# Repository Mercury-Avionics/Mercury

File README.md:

# Mercury
Integrated Avionics Package for Rocket and UAV Needs
Built on STM32 F4

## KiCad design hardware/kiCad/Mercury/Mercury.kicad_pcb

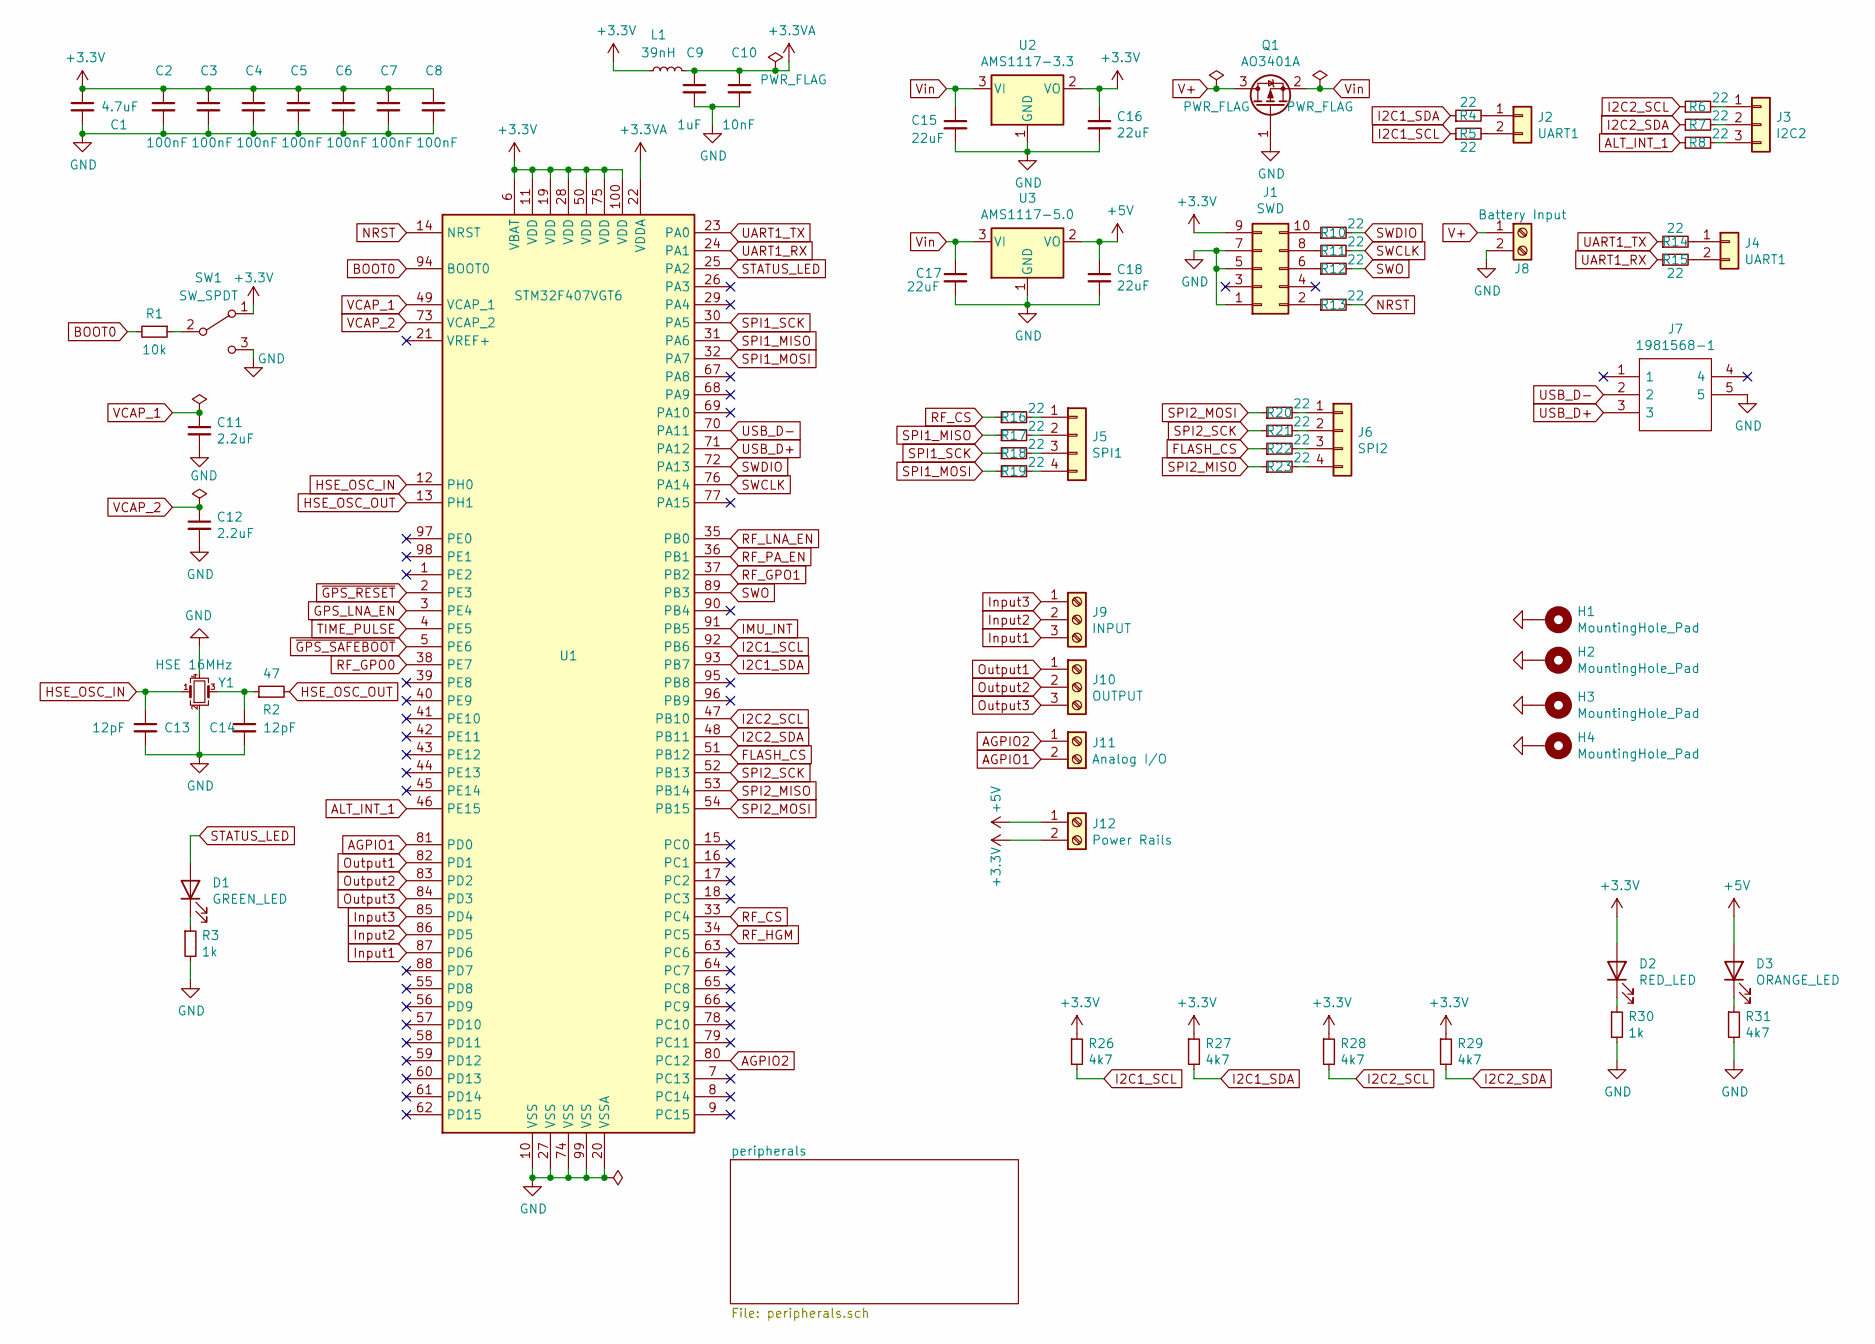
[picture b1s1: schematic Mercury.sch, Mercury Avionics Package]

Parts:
C1: 4.7uF; C_0805_2012Metric; LCSC Part # C1779
C2, C3, C4, C5, C6, C7, C8: 100nF; C_0402_1005Metric; LCSC Part # C1525
C9: 1uF; C_0402_1005Metric; LCSC Part # C52923
C10: 10nF; C_0402_1005Metric; LCSC Part # C15195
C11, C12: 2.2uF; C_0603_1608Metric; LCSC Part # C23630
C13, C14: 12pF; C_0402_1005Metric; LCSC Part # C1547
C15, C16, C17, C18: 22uF; C_0805_2012Metric; LCSC Part # C45783
D1: GREEN_LED; LED_0603_1608Metric; LCSC Part # C72043
D2: RED_LED; LED_0603_1608Metric; LCSC Part # C2286
D3: ORANGE_LED; LED_0603_1608Metric; LCSC Part # C375450
H1, H2, H3, H4: MountingHole_Pad; MountingHole_3mm_Pad_Via
J1: SWD; PinHeader_2x05_P1.27mm_Vertical
J2, J4: UART1; SolderWire-0.1sqmm_1x02_P3.6mm_D0.4mm_OD1mm
J3: I2C2; SolderWire-0.1sqmm_1x03_P3.6mm_D0.4mm_OD1mm
J5: SPI1; SolderWire-0.1sqmm_1x04_P3.6mm_D0.4mm_OD1mm
J6: SPI2; SolderWire-0.1sqmm_1x04_P3.6mm_D0.4mm_OD1mm
J7: 1981568-1; Mouser Part Number 571-1981568-1
J8: Battery Input; TerminalBlock_Phoenix_MKDS-1,5-2-5.08_1x02_P5.08mm_Horizont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
J9: INPUT; TerminalBlock_Phoenix_MKDS-1,5-3-5.08_1x03_P5.08mm_Horizont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
J10: OUTPUT; TerminalBlock_Phoenix_MKDS-1,5-3-5.08_1x03_P5.08mm_Horizont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
J11: Analog I/O; TerminalBlock_Phoenix_MKDS-1,5-2-5.08_1x02_P5.08mm_Horizont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
J12: Power Rails; TerminalBlock_Phoenix_MKDS-1,5-2-5.08_1x02_P5.08mm_Horizont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
L1: 39nH; L_0402_1005Metric; LCSC Part # C26443
Q1: AO3401A; SOT-23; LCSC Part # C15127
R1: 10k; R_0402_1005Metric; LCSC Part # C25744
R2: 47; R_0805_2012Metric; LCSC Part # C17714
R3, R30: 1k; R_0402_1005Metric; LCSC Part # C11702
R4, R5, R6, R7, R8, R10, R11, R12, R13, R14, R15, R16, R17, R18, R19, R20, R21, R22, R23: 22; R_0402_1005Metric; LCSC Part # C25092
R26, R27, R28, R29, R31: 4k7; R_0402_1005Metric; LCSC Part # C25900
SW1: SW_SPDT; SW_CuK_OS102011MA1QN1_SPDT_Angled
U1: STM32F407VGT6; LQFP-100_14x14mm_P0.5mm; LCSC Part # C12345
U2: AMS1117-3.3; SOT-223-3_TabPin2; LCSC Part # C6186
U3: AMS1117-5.0; SOT-223-3_TabPin2; LCSC Part # C6187
Y1: HSE 16MHz; Crystal_SMD_3225-4Pin_3.2x2.5mm; LCSC Part # C13738

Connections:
+3.3VA: C9.1, C10.1, L1.2, U1.22 (VDDA)
+3V3: C1.1, C2.1, C3.1, C4.1, C5.1, C6.1, C7.1, C8.1, C16.1, D2.2 (A), J1.9, J12.2, L1.1, R26.1, R27.1, R28.1, R29.1, SW1.1 (A), U1.6 (VBAT), U1.11 (VDD), U1.19 (VDD), U1.28 (VDD), U1.50 (VDD), U1.75 (VDD), U1.100 (VDD), U2.2 (VO); also elsewhere on the board
+5V: C18.1, D3.2 (A), J12.1, U3.2 (VO)
AGPIO1: J11.2, U1.81 (PD0)
AGPIO2: J11.1, U1.80 (PC12)
ALT_INT_1: R8.1, U1.46 (PE15); also elsewhere on the board
BOOT0: R1.2, U1.94 (BOOT0)
FLASH_CS: R22.1, U1.51 (PB12); also elsewhere on the board
GND: C1.2, C2.2, C3.2, C4.2, C5.2, C6.2, C7.2, C8.2, C9.2, C10.2, C11.2, C12.2, C13.2, C14.2, C15.2, C16.2, C17.2, C18.2, H1.1, H2.1, H3.1, H4.1, J1.1, J1.5, J1.7, J7.5, J8.2, Q1.1 (G), R3.2, R30.2, R31.2, SW1.3 (C), U1.10 (VSS), U1.20 (VSSA), U1.27 (VSS), U1.74 (VSS), U1.99 (VSS), U2.1 (GND), U3.1 (GND), Y1.2, Y1.4; also elsewhere on the board
GPS_LNA_EN: U1.3 (PE4); also elsewhere on the board
HSE_OSC_IN: C13.1, U1.12 (PH0), Y1.1
HSE_OSC_OUT: R2.2, U1.13 (PH1)
I2C1_SCL: R5.1, R26.2, U1.92 (PB6); also elsewhere on the board
I2C1_SDA: R4.1, R27.2, U1.93 (PB7); also elsewhere on the board
I2C2_SCL: R6.1, R28.2, U1.47 (PB10); also elsewhere on the board
I2C2_SDA: R7.1, R29.2, U1.48 (PB11); also elsewhere on the board
IMU_INT: U1.91 (PB5); also elsewhere on the board
Input1: J9.3, U1.87 (PD6)
Input2: J9.2, U1.86 (PD5)
Input3: J9.1, U1.85 (PD4)
NRST: R13.2, U1.14 (NRST)
unnamed: C14.1, R2.1, Y1.3
unnamed: D1.1 (K), R3.1
unnamed: D2.1 (K), R30.1
unnamed: D3.1 (K), R31.1
unnamed: J1.2, R13.1
unnamed: J1.6, R12.1
unnamed: J1.8, R11.1
unnamed: J1.10, R10.1
unnamed: J2.1, R4.2
unnamed: J2.2, R5.2
unnamed: J3.1, R6.2
unnamed: J3.2, R7.2
unnamed: J3.3, R8.2
unnamed: J4.1, R14.2
unnamed: J4.2, R15.2
unnamed: J5.1, R16.2
unnamed: J5.2, R17.2
unnamed: J5.3, R18.2
unnamed: J5.4, R19.2
unnamed: J6.1, R20.2
unnamed: J6.2, R21.2
unnamed: J6.3, R22.2
unnamed: J6.4, R23.2
unnamed: R1.1, SW1.2 (B)
Output1: J10.1, U1.82 (PD1)
Output2: J10.2, U1.83 (PD2)
Output3: J10.3, U1.84 (PD3)
RF_CS: R16.1, U1.33 (PC4); also elsewhere on the board
RF_GPO0: U1.38 (PE7); also elsewhere on the board
RF_GPO1: U1.37 (PB2); also elsewhere on the board
RF_HGM: U1.34 (PC5); also elsewhere on the board
RF_LNA_EN: U1.35 (PB0); also elsewhere on the board
RF_PA_EN: U1.36 (PB1); also elsewhere on the board
SPI1_MISO: R17.1, U1.31 (PA6); also elsewhere on the board
SPI1_MOSI: R19.1, U1.32 (PA7); also elsewhere on the board
SPI1_SCK: R18.1, U1.30 (PA5); also elsewhere on the board
SPI2_MISO: R23.1, U1.53 (PB14); also elsewhere on the board
SPI2_MOSI: R20.1, U1.54 (PB15); also elsewhere on the board
SPI2_SCK: R21.1, U1.52 (PB13); also elsewhere on the board
STATUS_LED: D1.2 (A), U1.25 (PA2)
SWCLK: R11.2, U1.76 (PA14)
SWDIO: R10.2, U1.72 (PA13)
SWO: R12.2, U1.89 (PB3)
TIME_PULSE: U1.4 (PE5); also elsewhere on the board
UART1_RX: R15.1, U1.24 (PA1); also elsewhere on the board
UART1_TX: R14.1, U1.23 (PA0); also elsewhere on the board
USB_D+: J7.3, U1.71 (PA12)
USB_D-: J7.2, U1.70 (PA11)
V+: J8.1, Q1.3 (D)
VCAP_1: C11.1, U1.49 (VCAP_1)
VCAP_2: C12.1, U1.73 (VCAP_2)
Vin: C15.1, C17.1, Q1.2 (S), U2.3 (VI), U3.3 (VI)
~GPS_RESET: U1.2 (PE3); also elsewhere on the board
~GPS_SAFEBOOT: U1.5 (PE6); also elsewhere on the board

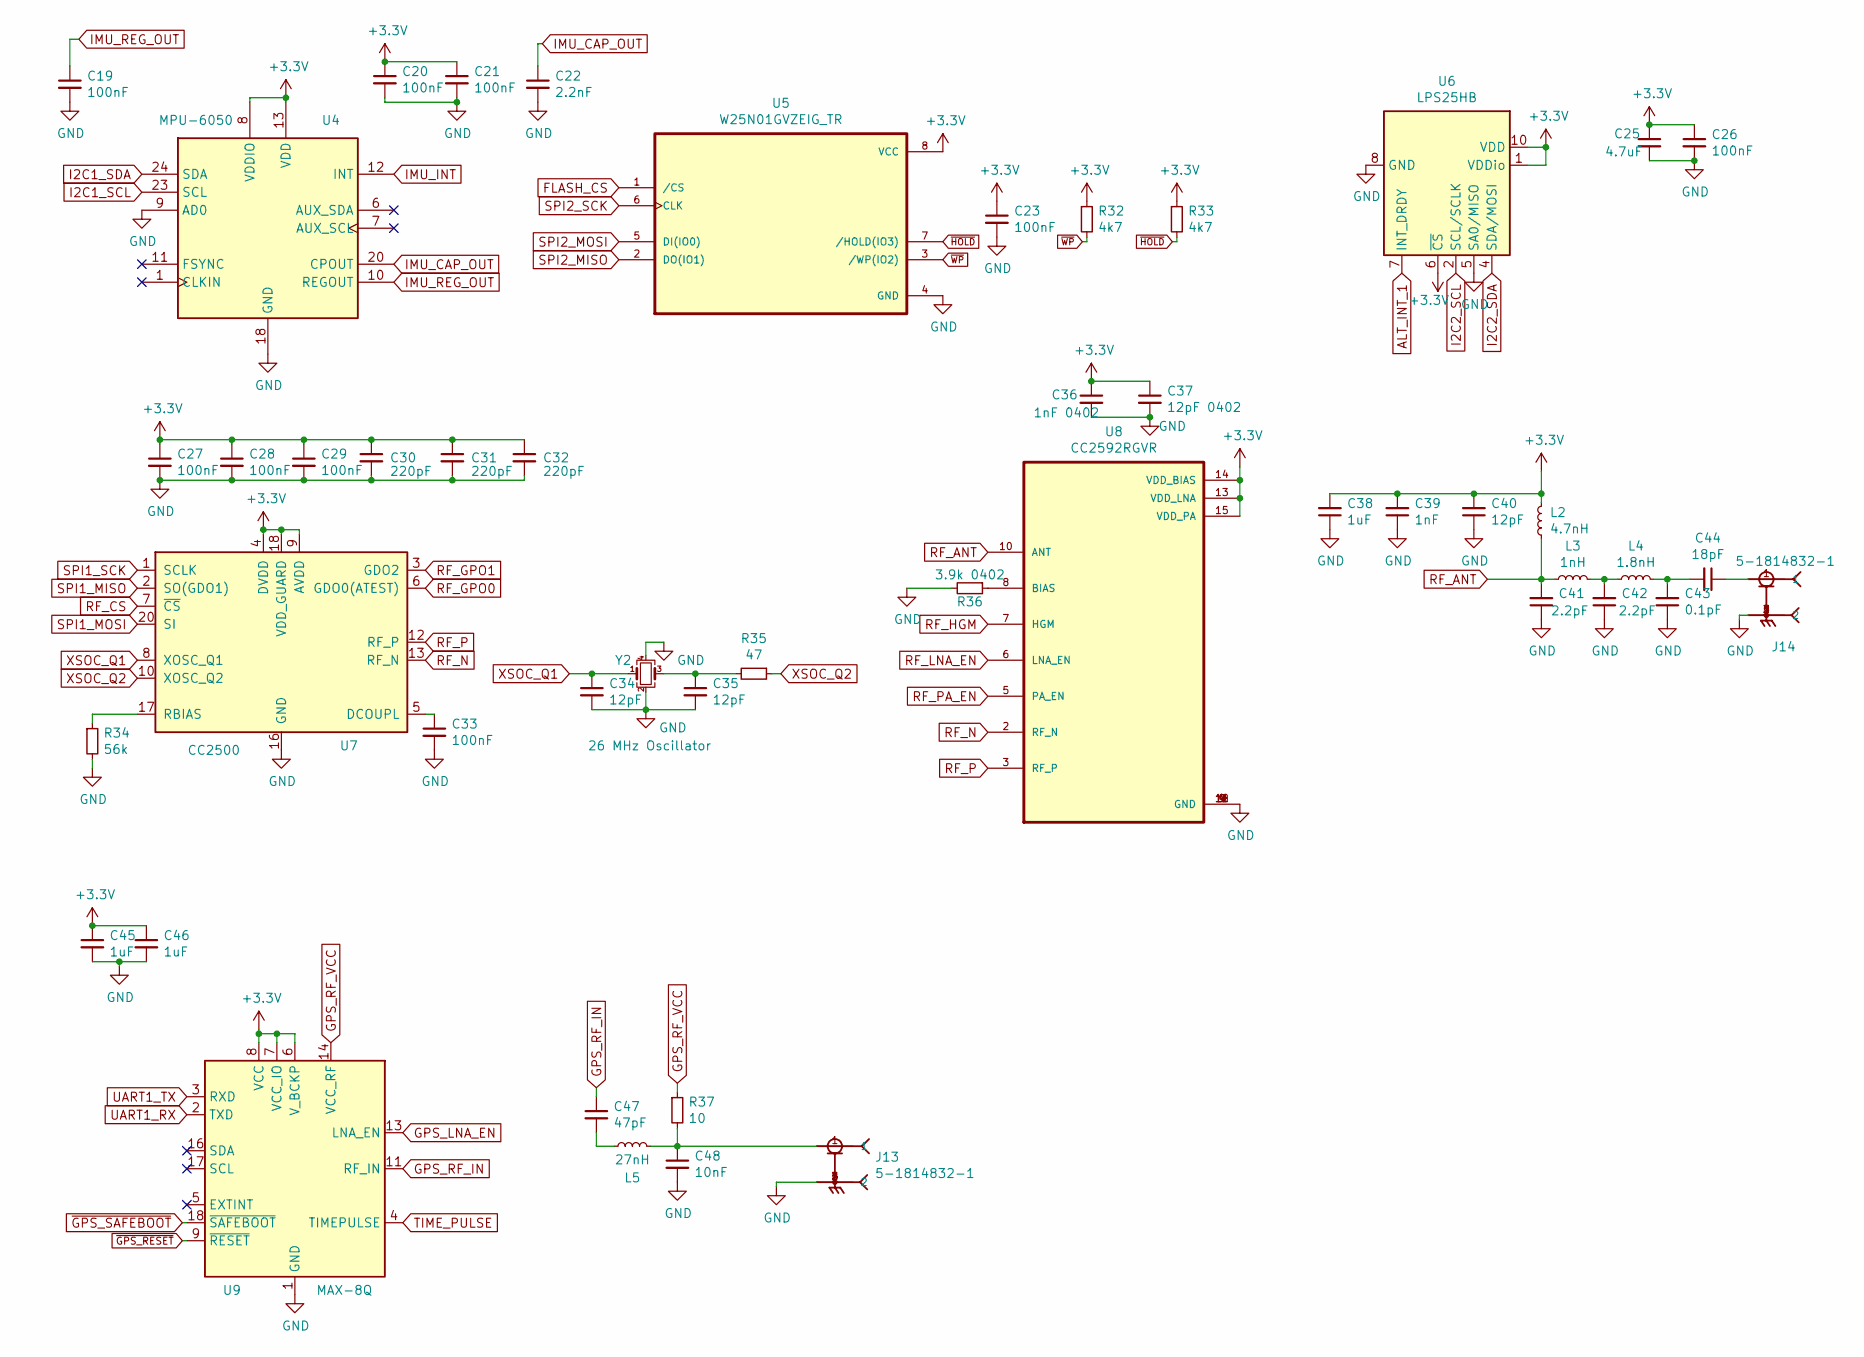
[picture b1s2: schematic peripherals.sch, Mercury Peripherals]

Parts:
C19, C20, C21, C23, C27, C28, C29, C33: 100nF; C_0402_1005Metric; LCSC Part # C1525
C22: 2.2nF; C_0603_1608Metric; LCSC Part # C1604
C25: 4.7uF; C_0805_2012Metric; LCSC Part # C1779
C26: 100nF; C_0603_1608Metric; LCSC Part # C14663
C30, C31, C32: 220pF; C_0402_1005Metric; LCSC Part # C1530
C34, C35, C40: 12pF; C_0402_1005Metric; LCSC Part # C1547
C36: 1nF 0402; C_0402_1005Metric; LCSC Part # C1523
C37: 12pF 0402; C_0402_1005Metric; LCSC Part # C1547
C38, C45, C46: 1uF; C_0402_1005Metric; LCSC Part # C52923
C39: 1nF; C_0402_1005Metric; LCSC Part # C1523
C41, C42: 2.2pF; C_0402_1005Metric; LCSC Part # C1559
C43: 0.1pF; C_0402_1005Metric; LCSC Part # C161338
C44: 18pF; C_0402_1005Metric; LCSC Part # C1549
C47: 47pF; C_0402_1005Metric; LCSC Part # C1567
C48: 10nF; C_0402_1005Metric; LCSC Part # C15195
J13, J14: 5-1814832-1; TE_5-1814832-1
L2: 4.7nH; L_0402_1005Metric; LCSC Part # C13595
L3: 1nH; L_0402_1005Metric; LCSC Part # C18222
L4: 1.8nH; L_0402_1005Metric; LCSC Part # C18304
L5: 27nH; L_0402_1005Metric; LCSC Part # C18830
R32, R33: 4k7; R_0402_1005Metric; LCSC Part # C25900
R34: 56k; R_0402_1005Metric; LCSC Part # C25796
R35: 47; R_0402_1005Metric; LCSC Part # C25118
R36: 3.9k 0402; R_0402_1005Metric; LCSC Part # C51721
R37: 10; R_0402_1005Metric; LCSC Part # C25744
U4: MPU-6050; InvenSense_QFN-24_4x4mm_P0.5mm; LCSC Part # C24112
U5: W25N01GVZEIG_TR; SON127P800X600X80-9N; LCSC Part # C88868
U6: LPS25HB; ST_HLGA-10_2.5x2.5mm_P0.6mm_LayoutBorder3x2y; LCSC Part # C87898
U7: CC2500; Texas_S-PVQFN-N20_EP2.4x2.4mm; LCSC Part # C57494
U8: CC2592RGVR; QFN65P400X400X100-17N; LCSC Part # C53274
U9: MAX-8Q; ublox_MAX
Y2: 26 MHz Oscillator; Crystal_SMD_3225-4Pin_3.2x2.5mm; LCSC Part # C23425

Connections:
+3V3: C20.1, C21.1, C23.1, C25.1, C26.1, C27.1, C28.1, C29.1, C30.1, C31.1, C32.1, C36.1, C37.1, C38.2, C39.2, C40.2, C45.1, C46.1, L2.2, R32.1, R33.1, U4.8 (VDDIO), U4.13 (VDD), U5.8 (VCC), U6.1 (VDDio), U6.6 (~CS), U6.10 (VDD), U7.4 (DVDD), U7.9 (AVDD), U7.11 (AVDD), U7.14 (AVDD), U7.15 (AVDD), U7.18 (VDD_GUARD), U8.13 (VDD_LNA), U8.14 (VDD_BIAS), U8.15 (VDD_PA), U9.6 (V_BCKP), U9.7 (VCC_IO), U9.8 (VCC); also elsewhere on the board
ALT_INT_1: U6.7 (INT_DRDY); also elsewhere on the board
FLASH_CS: U5.1 (/CS); also elsewhere on the board
GND: C19.2, C20.2, C21.2, C22.2, C23.2, C25.2, C26.2, C27.2, C28.2, C29.2, C30.2, C31.2, C32.2, C33.2, C34.2, C35.2, C36.2, C37.2, C38.1, C39.1, C40.1, C41.1, C42.1, C43.1, C45.2, C46.2, C48.2, J13.2, J13.3 (2), J13.4 (2), J13.5 (2), J14.2, J14.3 (2), J14.4 (2), J14.5 (2), R34.2, R36.2, U4.9 (AD0), U4.18 (GND), U5.4 (GND), U6.3 (GND), U6.5 (SA0/MISO), U6.8 (GND), U6.9 (GND), U7.16 (GND), U7.19 (GND), U7.21 (GND), U8.1 (GND), U8.4 (GND), U8.9 (GND), U8.11 (GND), U8.12 (GND), U8.16 (GND), U9.1 (GND), U9.10 (GND), U9.12 (GND), Y2.2, Y2.4; also elsewhere on the board
GPS_LNA_EN: U9.13 (LNA_EN); also elsewhere on the board
GPS_RF_IN: C47.1, U9.11 (RF_IN)
GPS_RF_VCC: R37.1, U9.14 (VCC_RF)
I2C1_SCL: U4.23 (SCL); also elsewhere on the board
I2C1_SDA: U4.24 (SDA); also elsewhere on the board
I2C2_SCL: U6.2 (SCL/SCLK); also elsewhere on the board
I2C2_SDA: U6.4 (SDA/MOSI); also elsewhere on the board
IMU_CAP_OUT: C22.1, U4.20 (CPOUT)
IMU_INT: U4.12 (INT); also elsewhere on the board
IMU_REG_OUT: C19.1, U4.10 (REGOUT)
unnamed: C33.1, U7.5 (DCOUPL)
unnamed: C35.1, R35.2, Y2.3
unnamed: C42.2, L3.2, L4.1
unnamed: C43.2, C44.2, L4.2
unnamed: C44.1, J14.1
unnamed: C47.2, L5.1
unnamed: C48.1, J13.1, L5.2, R37.2
unnamed: R34.1, U7.17 (RBIAS)
unnamed: R36.1, U8.8 (BIAS)
RF_ANT: C41.2, L2.1, L3.1, U8.10 (ANT)
RF_CS: U7.7 (~CS~); also elsewhere on the board
RF_GPO0: U7.6 (GDO0(ATEST)); also elsewhere on the board
RF_GPO1: U7.3 (GDO2); also elsewhere on the board
RF_HGM: U8.7 (HGM); also elsewhere on the board
RF_LNA_EN: U8.6 (LNA_EN); also elsewhere on the board
RF_N: U7.13 (RF_N), U8.2 (RF_N)
RF_P: U7.12 (RF_P), U8.3 (RF_P)
RF_PA_EN: U8.5 (PA_EN); also elsewhere on the board
SPI1_MISO: U7.2 (SO(GDO1)); also elsewhere on the board
SPI1_MOSI: U7.20 (SI); also elsewhere on the board
SPI1_SCK: U7.1 (SCLK); also elsewhere on the board
SPI2_MISO: U5.2 (DO(IO1)); also elsewhere on the board
SPI2_MOSI: U5.5 (DI(IO0)); also elsewhere on the board
SPI2_SCK: U5.6 (CLK); also elsewhere on the board
TIME_PULSE: U9.4 (TIMEPULSE); also elsewhere on the board
UART1_RX: U9.2 (TXD); also elsewhere on the board
UART1_TX: U9.3 (RXD); also elsewhere on the board
XSOC_Q1: C34.1, U7.8 (XOSC_Q1), Y2.1
XSOC_Q2: R35.1, U7.10 (XOSC_Q2)
~GPS_RESET: U9.9 (~RESET); also elsewhere on the board
~GPS_SAFEBOOT: U9.18 (~SAFEBOOT); also elsewhere on the board
~HOLD: R33.2, U5.7 (/HOLD(IO3))
~WP: R32.2, U5.3 (/WP(IO2))

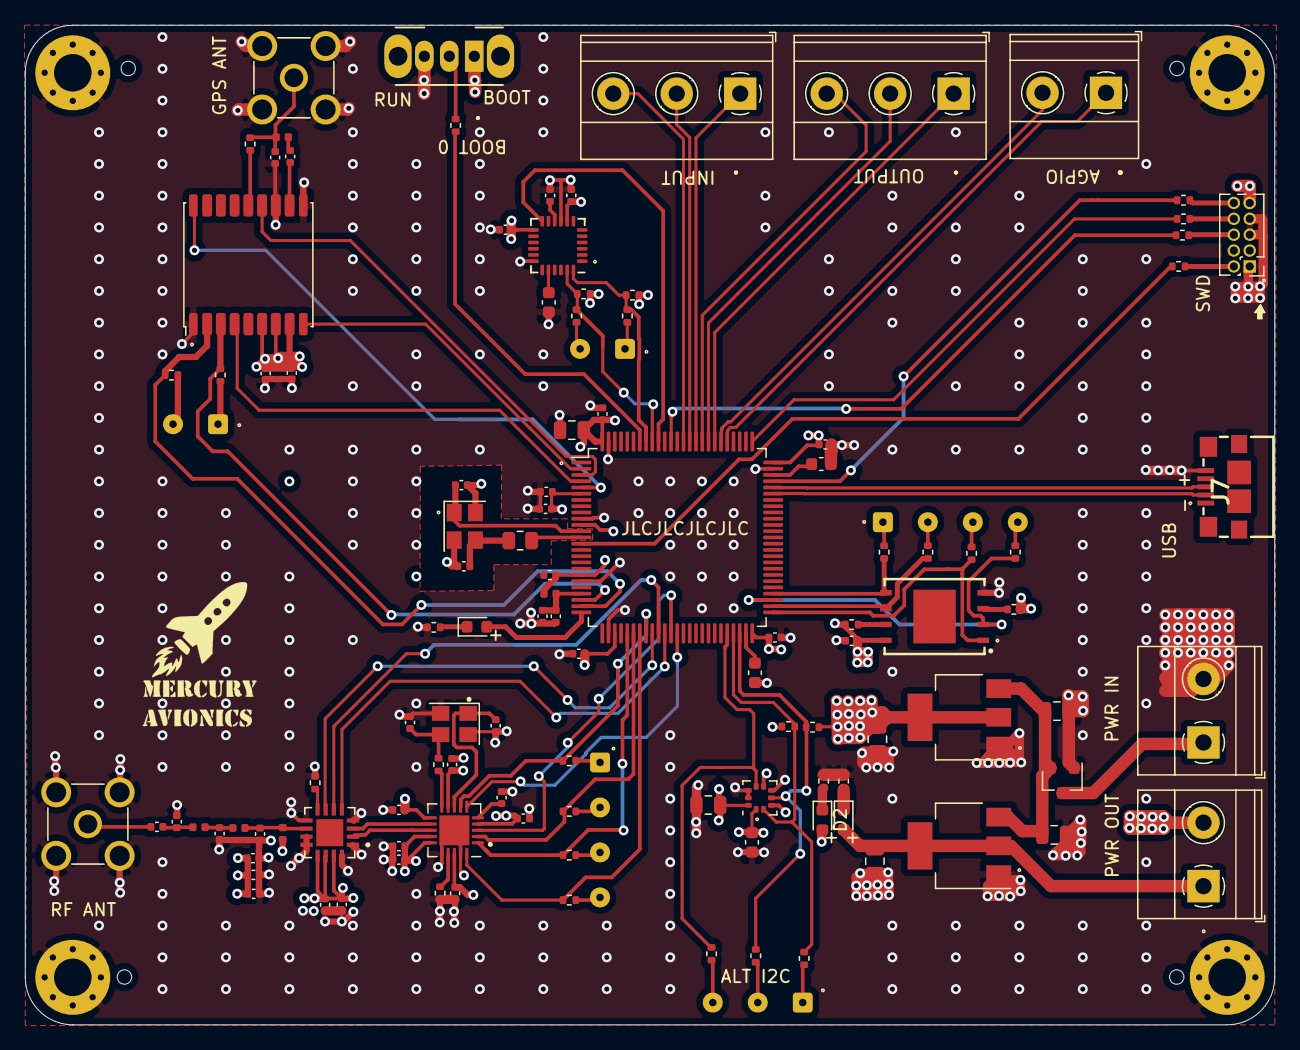
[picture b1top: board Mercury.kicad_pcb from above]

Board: 4 copper layers, 100.0 x 80.0 mm, 121 parts (0 on the bottom side), 95 nets.

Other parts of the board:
G1: LOGO

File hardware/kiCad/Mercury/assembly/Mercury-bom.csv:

Comment,Designator,Footprint,LCSC Part #
"4.7uF Unpolarized capacitor, small symbol","C1,C25",C_0805_2012Metric,C1779
"100nF Unpolarized capacitor, small symbol","C2,C3,C4,C5,C6,C7,C8,C19,C20,C21,C23,C27,C28,C29,C33",C_0402_1005Metric,C1525
"1uF Unpolarized capacitor, small symbol","C9,C38,C45,C46",C_0402_1005Metric,C52923
"10nF Unpolarized capacitor, small symbol","C10,C48",C_0402_1005Metric,C15195
"2.2uF Unpolarized capacitor, small symbol","C11,C12",C_0603_1608Metric,C23630
"12pF Unpolarized capacitor, small symbol","C13,C14,C34,C35,C40",C_0402_1005Metric,C1547
"22uF Unpolarized capacitor, small symbol","C15,C16,C17,C18",C_0805_2012Metric,C45783
"2.2nF Unpolarized capacitor, small symbol",C22,C_0603_1608Metric,C1604
"100nF Unpolarized capacitor, small symbol",C26,C_0603_1608Metric,C14663
"220pF Unpolarized capacitor, small symbol","C30,C31,C32",C_0402_1005Metric,C1530
"1nF 0402 Unpolarized capacitor, small symbol",C36,C_0402_1005Metric,C1523
"12pF 0402 Unpolarized capacitor, small symbol",C37,C_0402_1005Metric,C1547
"1nF Unpolarized capacitor, small symbol",C39,C_0402_1005Metric,C1523
"2.2pF Unpolarized capacitor, small symbol","C41,C42",C_0402_1005Metric,C1559
"0.1pF Unpolarized capacitor, small symbol",C43,C_0402_1005Metric,C161338
"18pF Unpolarized capacitor, small symbol",C44,C_0402_1005Metric,C1549
"47pF Unpolarized capacitor, small symbol",C47,C_0402_1005Metric,C1567
GREEN_LED Light emitting diode,D1,LED_0603_1608Metric,C72043
RED_LED Light emitting diode,D2,LED_0603_1608Metric,C2286
ORANGE_LED Light emitting diode,D3,LED_0603_1608Metric,C375450
MountingHole_Pad Mounting Hole with connection,"H1,H2,H3,H4",MountingHole_3mm_Pad_Via,
"SWD Generic connector, double row, 02x05, odd/even pin numbering scheme (row 1 odd numbers, row 2 even numbers), script generated (kicad-library-utils/schlib/autogen/connector/)",J1,PinHeader_2x05_P1.27mm_Vertical,
"UART1 Generic connector, single row, 01x02, script generated (kicad-library-utils/schlib/autogen/connector/)","J2,J4",SolderWire-0.1sqmm_1x02_P3.6mm_D0.4mm_OD1mm,
"I2C2 Generic connector, single row, 01x03, script generated (kicad-library-utils/schlib/autogen/connector/)",J3,SolderWire-0.1sqmm_1x03_P3.6mm_D0.4mm_OD1mm,
"SPI1 Generic connector, single row, 01x04, script generated (kicad-library-utils/schlib/autogen/connector/)",J5,SolderWire-0.1sqmm_1x04_P3.6mm_D0.4mm_OD1mm,
"SPI2 Generic connector, single row, 01x04, script generated (kicad-library-utils/schlib/autogen/connector/)",J6,SolderWire-0.1sqmm_1x04_P3.6mm_D0.4mm_OD1mm,
1981568-1 ,J7,1981568-1,
"Battery Input Generic screw terminal, single row, 01x02, script generated (kicad-library-utils/schlib/autogen/connector/)",J8,"TerminalBlock_Phoenix_MKDS-1,5-2-5.08_1x02_P5.08mm_Horizontal",
"INPUT Generic screw terminal, single row, 01x03, script generated (kicad-library-utils/schlib/autogen/connector/)",J9,"TerminalBlock_Phoenix_MKDS-1,5-3-5.08_1x03_P5.08mm_Horizontal",
"OUTPUT Generic screw terminal, single row, 01x03, script generated (kicad-library-utils/schlib/autogen/connector/)",J10,"TerminalBlock_Phoenix_MKDS-1,5-3-5.08_1x03_P5.08mm_Horizontal",
"Analog I/O Generic screw terminal, single row, 01x02, script generated (kicad-library-utils/schlib/autogen/connector/)",J11,"TerminalBlock_Phoenix_MKDS-1,5-2-5.08_1x02_P5.08mm_Horizontal",
"Power Rails Generic screw terminal, single row, 01x02, script generated (kicad-library-utils/schlib/autogen/connector/)",J12,"TerminalBlock_Phoenix_MKDS-1,5-2-5.08_1x02_P5.08mm_Horizontal",
5-1814832-1 ,"J13,J14",TE_5-1814832-1,
"39nH Inductor, small symbol",L1,L_0402_1005Metric,C26443
"4.7nH Inductor, small symbol",L2,L_0402_1005Metric,C13595
"1nH Inductor, small symbol",L3,L_0402_1005Metric,C18222
"1.8nH Inductor, small symbol",L4,L_0402_1005Metric,C18304
"27nH Inductor, small symbol",L5,L_0402_1005Metric,C18830
"AO3401A -4.0A Id, -30V Vds, P-Channel MOSFET, SOT-23",Q1,SOT-23,C15127
"10k Resistor, small symbol",R1,R_0402_1005Metric,C25744
"47 Resistor, small symbol",R2,R_0805_2012Metric,C17714
"1k Resistor, small symbol","R3,R30",R_0402_1005Metric,C11702
"22 Resistor, small symbol","R4,R5,R6,R7,R8,R10,R11,R12,R13,R14,R15,R16,R17,R18,R19,R20,R21,R22,R23",R_0402_1005Metric,C25092
"4k7 Resistor, small symbol","R26,R27,R28,R29,R31,R32,R33",R_0402_1005Metric,C25900
"56k Resistor, small symbol",R34,R_0402_1005Metric,C25796
"47 Resistor, small symbol",R35,R_0402_1005Metric,C25118
"3.9k 0402 Resistor, small symbol",R36,R_0402_1005Metric,C51721
"10 Resistor, small symbol",R37,R_0402_1005Metric,C25744
"SW_SPDT Switch, single pole double throw",SW1,SW_CuK_OS102011MA1QN1_SPDT_Angled,
"STM32F407VGT6 ARM Cortex-M4 MCU, 1024KB flash, 128KB RAM, 168MHz, 1.8-3.6V, 82 GPIO, LQFP-100",U1,LQFP-100_14x14mm_P0.5mm,C12345
"AMS1117-3.3 1A Low Dropout regulator, positive, 3.3V fixed output, SOT-223",U2,SOT-223-3_TabPin2,C6186
"AMS1117-5.0 1A Low Dropout regulator, positive, 5.0V fixed output, SOT-223",U3,SOT-223-3_TabPin2,C6187
"MPU-6050 InvenSense 6-Axis Motion Sensor, Gyroscope, Accelerometer, I2C",U4,InvenSense_QFN-24_4x4mm_P0.5mm,C24112
W25N01GVZEIG_TR ,U5,SON127P800X600X80-9N,C88868
"LPS25HB MEMS pressure sensor, 260-1260 hPa, absolute digital output baromeeter",U6,ST_HLGA-10_2.5x2.5mm_P0.6mm_LayoutBorder3x2y,C87898
"CC2500 Single Chip Low Power RF Transceiver, QFN-20",U7,Texas_S-PVQFN-N20_EP2.4x2.4mm,C57494
CC2592RGVR ,U8,QFN65P400X400X100-17N,C53274
"MAX-8Q GNSS Module M8, VCC 2.7V to 3.6V",U9,ublox_MAX,
"HSE 16MHz Four pin crystal, GND on pins 2 and 4, small symbol",Y1,Crystal_SMD_3225-4Pin_3.2x2.5mm,C13738
"26 MHz Oscillator Four pin crystal, GND on pins 2 and 4, small symbol",Y2,Crystal_SMD_3225-4Pin_3.2x2.5mm,C23425

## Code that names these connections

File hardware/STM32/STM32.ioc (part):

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Mcu.Name=STM32F407V(E-G)Tx
Mcu.Package=LQFP100
Mcu.UserName=STM32F407VGTx
PA0-WKUP.Mode=Asynchronous
PA0-WKUP.Signal=UART4_TX
PA1.Mode=Asynchronous
PA1.Signal=UART4_RX
PA11.Mode=Device_Only
PA11.Signal=USB_OTG_FS_DM
PA12.Mode=Device_Only
PA12.Signal=USB_OTG_FS_DP
PA13.Mode=Trace_Asynchronous_SW
PA13.Signal=SYS_JTMS-SWDIO
PA14.Mode=Trace_Asynchronous_SW
PA14.Signal=SYS_JTCK-SWCLK
PA2.Signal=GPIO_Output
PA5.Mode=Full_Duplex_Master
PA5.Signal=SPI1_SCK
PA6.Mode=Full_Duplex_Master
PA6.Signal=SPI1_MISO
PA7.Mode=Full_Duplex_Master
PA7.Signal=SPI1_MOSI
PA8.GPIOParameters=GPIO_Label
PA8.GPIO_Label=GPS_RESET
PA8.Signal=GPIO_Output
PB0.GPIOParameters=GPIO_Label
PB0.GPIO_Label=RF_LNA_EN
PB0.Signal=GPIO_Output
PB1.GPIOParameters=GPIO_Label
PB1.GPIO_Label=RF_PA_EN
PB1.Signal=GPIO_Output
PB10.Mode=I2C
PB10.Signal=I2C2_SCL
PB11.Mode=I2C
PB11.Signal=I2C2_SDA
PB12.GPIOParameters=GPIO_Label
PB12.GPIO_Label=FLASH_CS
PB12.Signal=GPIO_Output
PB13.Mode=Full_Duplex_Master
PB13.Signal=SPI2_SCK
PB14.Mode=Full_Duplex_Master
PB14.Signal=SPI2_MISO
PB15.Mode=Full_Duplex_Master
PB15.Signal=SPI2_MOSI
PB2.GPIOParameters=GPIO_Label
PB2.GPIO_Label=RF_GPO1
PB2.Signal=GPIO_Input
PB3.Mode=Trace_Asynchronous_SW
PB3.Signal=SYS_JTDO-SWO
PB5.GPIOParameters=GPIO_Label
PB5.GPIO_Label=IMU_INT
PB5.Signal=GPIO_Input
PB6.Mode=I2C
PB6.Signal=I2C1_SCL
PB7.Mode=I2C
PB7.Signal=I2C1_SDA
PC12.GPIOParameters=GPIO_Label
PC12.GPIO_Label=AGPIO2
PC12.Signal=GPIO_Analog
PC4.GPIOParameters=GPIO_Label
PC4.GPIO_Label=RF_CS
PC4.Signal=GPIO_Output
PC5.GPIOParameters=GPIO_Label
PC5.GPIO_Label=RF_HGM
PC5.Signal=GPIO_Output
PC7.GPIOParameters=GPIO_Label
PC7.GPIO_Label=GPS_SAFEBOOT
PC7.Signal=GPIO_Output
PC8.GPIOParameters=GPIO_Label
PC8.GPIO_Label=LNA_EN
PC8.Signal=GPIO_Output
PC9.GPIOParameters=GPIO_Label
PC9.GPIO_Label=TIME_PULSE
PC9.Signal=GPIO_Input
PD0.GPIOParameters=GPIO_Label
PD0.GPIO_Label=AGPIO1
PD0.Signal=GPIO_Analog
PD1.GPIOParameters=GPIO_Label
PD1.GPIO_Label=Output3
PD1.Signal=GPIO_Output
PD2.GPIOParameters=GPIO_Label
PD2.GPIO_Label=Output2
PD2.Signal=GPIO_Output
PD3.GPIOParameters=GPIO_Label
PD3.GPIO_Label=Output1
PD3.Signal=GPIO_Output
PD4.GPIOParameters=GPIO_Label
PD4.GPIO_Label=Input3
PD4.Signal=GPIO_Input
PD5.GPIOParameters=GPIO_Label
PD5.GPIO_Label=Input2
PD5.Signal=GPIO_Input
PD6.GPIOParameters=GPIO_Label
PD6.GPIO_Label=Input1
PD6.Signal=GPIO_Input
PE14.GPIOParameters=GPIO_Label
PE14.GPIO_Label=ALT_INT_2
PE14.Signal=GPIO_Output
PE15.GPIOParameters=GPIO_Label
PE15.GPIO_Label=ALT_INT_1
PE15.Signal=GPIO_Output
PE7.GPIOParameters=GPIO_Label
PE7.GPIO_Label=RF_GPO0
PE7.Signal=GPIO_Input
PH0-OSC_IN.Mode=HSE-External-Oscillator
PH0-OSC_IN.Signal=RCC_OSC_IN
PH1-OSC_OUT.Mode=HSE-External-Oscillator
PH1-OSC_OUT.Signal=RCC_OSC_OUT
RCC.HSE_VALUE=25000000
RCC.SYSCLKFreq_VALUE=16000000
board=custom

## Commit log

2021-01-06 Refresh
2021-01-06 Layout Done
2021-01-06 Added USB
2021-01-08 Layout + Routing v1 done
2021-01-12 Updated with final board design
2021-01-18 Sent For Manufacture
